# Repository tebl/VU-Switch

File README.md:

# Building VU Switch
All of this started when I found a really cool case on AliExpress, the *GOF-P01 133.4x55x109mm* and it all snowballed from that point. The one thing I actually needed was an audio input switcher so that I didn't have to swap the cables going into my 80s boombox, so I tried bying a ready-made module that in the end never fit into the case so I had to redesign the module to fit - then I added a VU Meter kit, mostly because I think they are really cool and I never had one before.

The first part of this project is therefore the passive audio switch, it allows up to four 3.5mm audio inputs that are switched to one output using relays. The PCB designed for it is the main part of this part, in addition to the documentation needed to actually build the complete unit.

The final part was the VU meter driver board and parts, those I'm using without any modification as the kit I bought on AliExpress (also available on Banggood and ebay) so far seems to work as intended. Just search for *2 Pcs VU Meter Warm Backlight Recording Audio Level Amp With Driver Module*, or any combination of those words and you should be able to find one for around 20$. The warm backlight described is actually a good old bulb, so they have a nice glow to them - you can see a video of the completed unit on [youtube.com](https://www.youtube.com/watch?v=rMdMJJwyIuU).

Going forward with this build, I'll be assuming you bought the same version of VU meters and case though you can substutute any parts as needed.

## Getting one
I won't be selling these, they're way too much to be making them for someone else. There will be an added project link for ordering the PCBs from [PCBWay](https://www.pcbway.com/setinvite.aspx?inviteid=88707), but you can use any PCB fabrication company by giving them the contents of the export directory (usually referred to as *gerber* files). 

Follow the links below for build instructions, the BOM and the relevant PCBWay shared projects belonging or associated with this project:
* [Building VU Switch](https://github.com/tebl/VU-Switch/blob/main/documentation/building.md) ([schematic](https://github.com/tebl/VU-Switch/tree/main/documentation/schematic))
* [PCBWay shared projects](https://www.pcbway.com/project/shareproject/?tag=VU%20Switch)

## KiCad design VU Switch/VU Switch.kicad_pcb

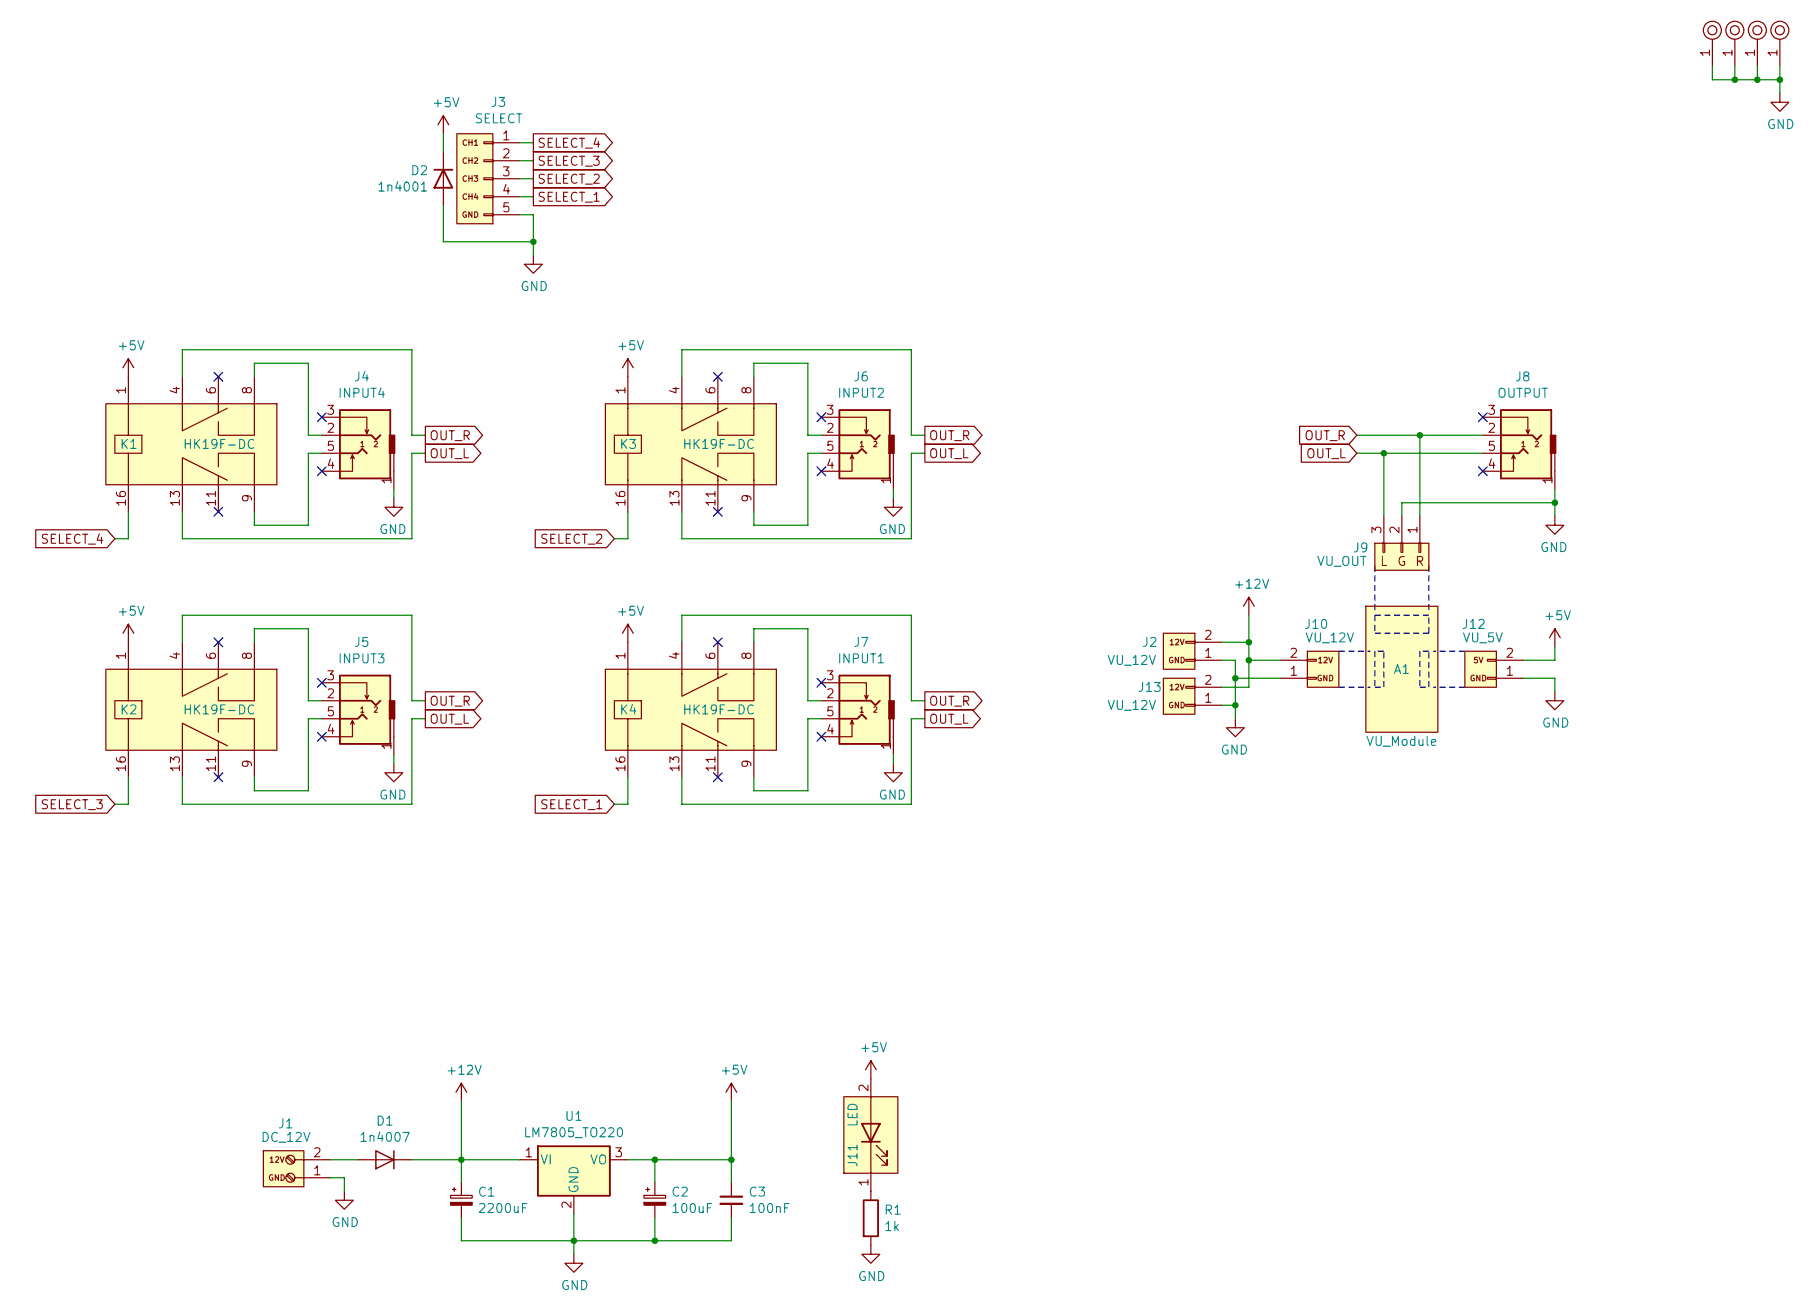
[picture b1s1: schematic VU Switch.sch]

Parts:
A1: VU_Module; VU_Driver_Board_5.0
C1: 2200uF; CP_Radial_D13.0mm_P5.00mm
C2: 100uF; CP_Radial_D6.3mm_P2.50mm
C3: 100nF; C_Disc_D4.7mm_W2.5mm_P5.00mm
D1: 1n4007; D_DO-41_SOD81_P10.16mm_Horizontal
D2: 1n4001; D_DO-41_SOD81_P10.16mm_Horizontal
J1: DC_12V; JST_XH_B2B-XH-A_1x02_P2.50mm_Vertical
J2, J10, J13: VU_12V; JST_XH_B2B-XH-A_1x02_P2.50mm_Vertical
J3: SELECT; JST_XH_B5B-XH-A_1x05_P2.50mm_Vertical
J4: INPUT4; Tayda_3.5mm_stereo_TRS_jack_A-853
J5: INPUT3; Tayda_3.5mm_stereo_TRS_jack_A-853
J6: INPUT2; Tayda_3.5mm_stereo_TRS_jack_A-853
J7: INPUT1; Tayda_3.5mm_stereo_TRS_jack_A-853
J8: OUTPUT; Tayda_3.5mm_stereo_TRS_jack_A-853
J9: VU_OUT; JST_XH_B3B-XH-A_1x03_P2.50mm_Vertical
J11: LED; JST_XH_B2B-XH-A_1x02_P2.50mm_Vertical
J12: VU_5V; JST_XH_B2B-XH-A_1x02_P2.50mm_Vertical
K1, K2, K3, K4: HK19F-DC
M1, M2, M3, M4: Mounting_pin; M3
R1: 1k; R_Axial_DIN0207_L6.3mm_D2.5mm_P10.16mm_Horizontal
U1: LM7805_TO220; TO-220-3_Vertical

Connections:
+5V: C2.1, C3.1, D2.1 (K), J11.2 (A), J12.2, K1.1, K2.1, K3.1, K4.1, U1.3 (VO)
+12V: C1.1, D1.1 (K), J2.2, J10.2, J13.2, U1.1 (VI)
GND: C1.2, C2.2, C3.2, D2.2 (A), J1.1, J2.1, J3.5, J4.1, J5.1, J6.1, J7.1, J8.1, J9.2, J10.1, J12.1, J13.1, M1.1, M2.1, M3.1, M4.1, R1.2, U1.2 (GND)
unnamed: D1.2 (A), J1.2
unnamed: J4.2, K1.8 (NO_1)
unnamed: J4.5, K1.9 (NO_2)
unnamed: J5.2, K2.8 (NO_1)
unnamed: J5.5, K2.9 (NO_2)
unnamed: J6.2, K3.8 (NO_1)
unnamed: J6.5, K3.9 (NO_2)
unnamed: J7.2, K4.8 (NO_1)
unnamed: J7.5, K4.9 (NO_2)
unnamed: J11.1 (K), R1.1
OUT_L: J8.5, J9.3, K1.13 (COM_2), K2.13 (COM_2), K3.13 (COM_2), K4.13 (COM_2)
OUT_R: J8.2, J9.1, K1.4 (COM_1), K2.4 (COM_1), K3.4 (COM_1), K4.4 (COM_1)
SELECT_1: J3.4, K4.16
SELECT_2: J3.3, K3.16
SELECT_3: J3.2, K2.16
SELECT_4: J3.1, K1.16

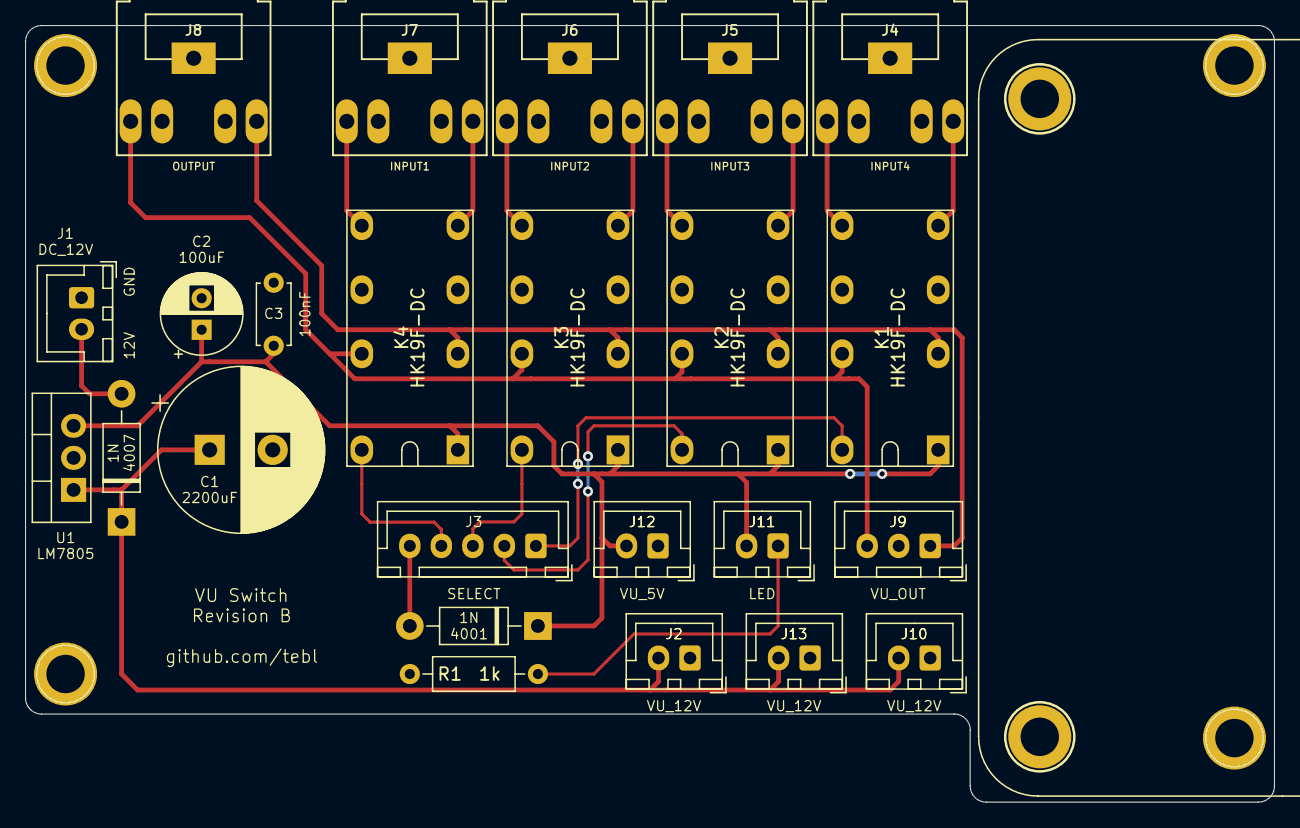
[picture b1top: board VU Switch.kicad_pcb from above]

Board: 2 copper layers, 99.1 x 61.6 mm, 29 parts (0 on the bottom side), 19 nets.

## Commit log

2021-01-17 Case dimensions
2021-01-17 Blank PCB
2021-01-18 Schematic done
2021-01-19 Assigned footprints
2021-01-19 Layout done
2021-01-26 Changed HK19 relay footprint to larger pads
2021-01-28 Tweaked audio jack position, changed power connector to XH.
2021-01-28 Updated gerber files
2021-01-28 Added gallery images
2021-01-28 Rearrange images
2021-01-28 VU driver hookup picture
2021-01-28 Added building.md
2021-01-28 Added chapter links
2021-01-28 Added main README
2021-01-28 Added main picture with power applied
2021-01-29 Added license label
2021-04-11 New pictures

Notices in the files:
VU Switch/VU Switch.kicad_pcb:
Licensed under
CERN OHL v1.2
